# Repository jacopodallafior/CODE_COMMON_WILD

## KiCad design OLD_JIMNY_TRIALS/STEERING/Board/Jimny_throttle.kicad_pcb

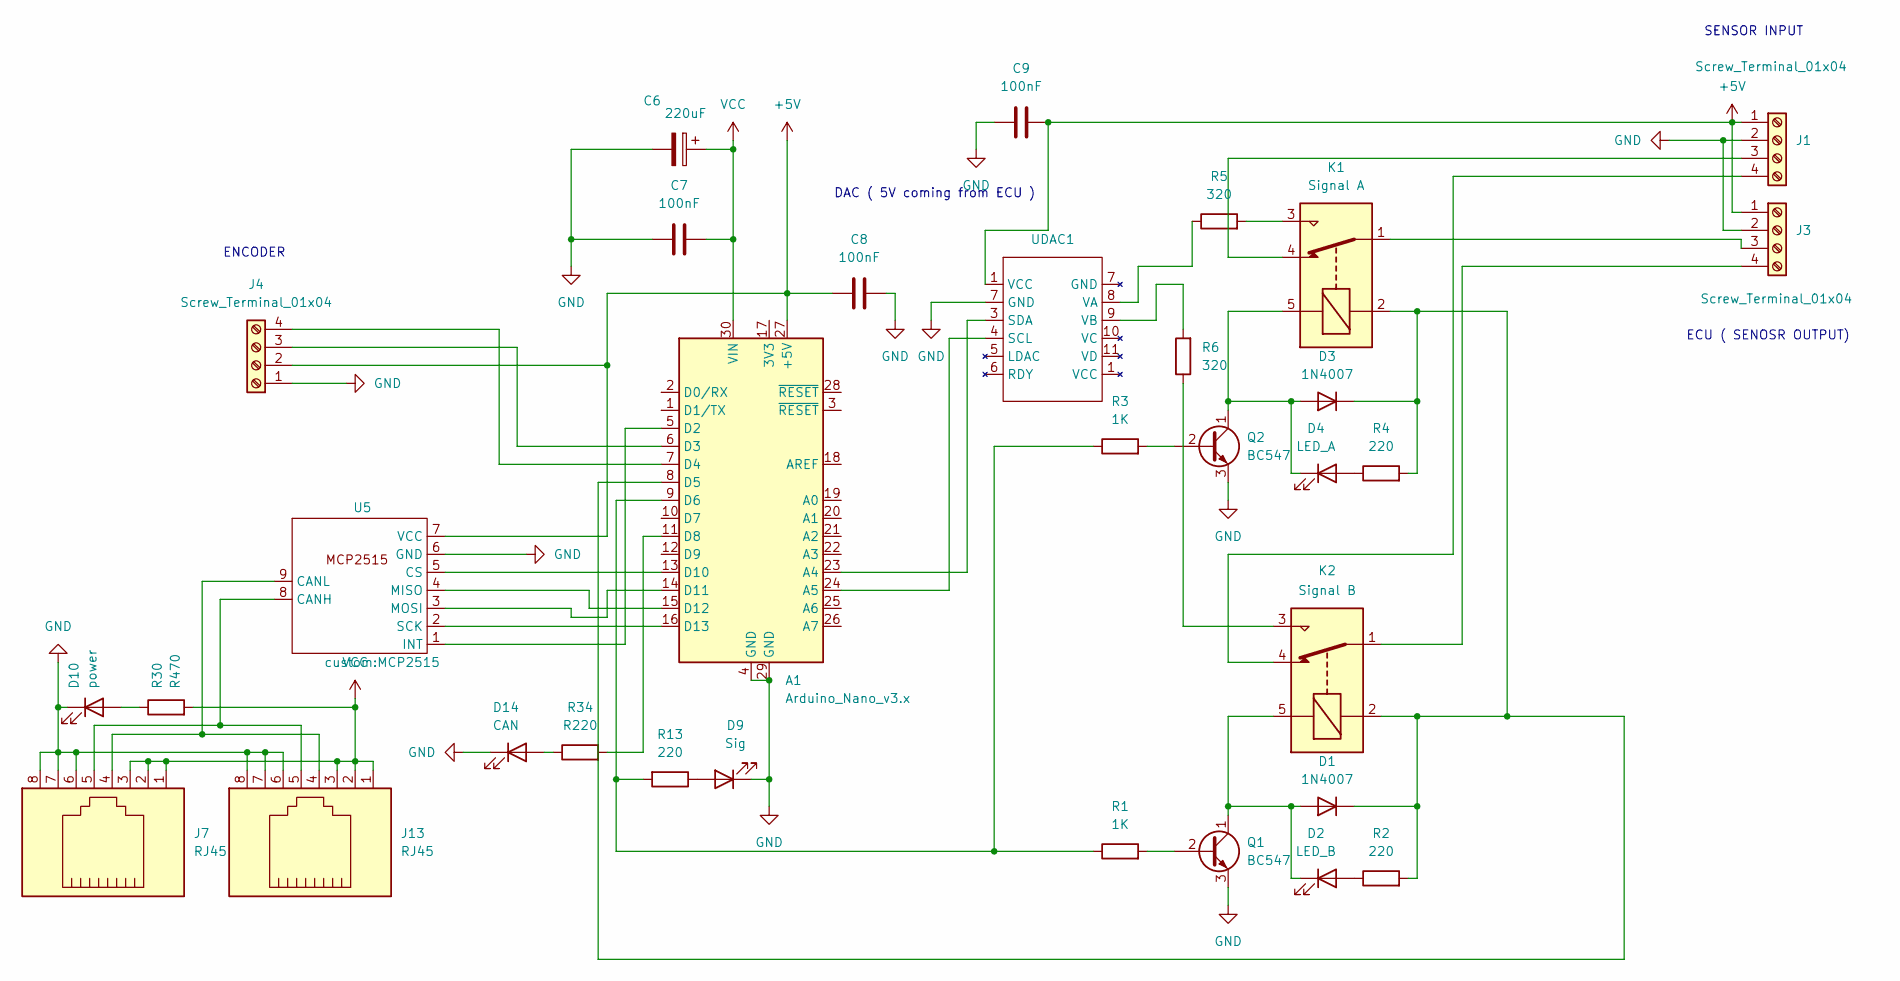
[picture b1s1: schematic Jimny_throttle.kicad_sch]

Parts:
A1: Arduino_Nano_v3.x; Arduino_Nano
C6: 220uF; CP_Radial_D8.0mm_P3.50mm
C7, C8, C9: 100nF; C_Rect_L4.6mm_W2.0mm_P2.50mm_MKS02_FKP02
D1, D3: 1N4007; D_DO-41_SOD81_P10.16mm_Horizontal
D2: LED_B; LED_D5.0mm
D4: LED_A; LED_D5.0mm
D9: Sig; LED_D5.0mm
D10: power; LED_D5.0mm
D14: CAN; LED_D5.0mm
J1, J3, J4: Screw_Terminal_01x04; TerminalBlock_Phoenix_MKDS-1,5-4_1x04_P5.00mm_Horizontal
J7, J13: RJ45; RJ45_OST_PJ012-8P8CX_Vertical
K1: Signal A; Relay_SPDT_SANYOU_SRD_Series_Form_C
K2: Signal B; Relay_SPDT_SANYOU_SRD_Series_Form_C
Q1, Q2: BC547; TO-92_Inline
R1, R3: 1K; R_Axial_DIN0207_L6.3mm_D2.5mm_P10.16mm_Horizontal
R2, R4, R13: 220; R_Axial_DIN0207_L6.3mm_D2.5mm_P10.16mm_Horizontal
R5, R6: 320; R_Axial_DIN0207_L6.3mm_D2.5mm_P10.16mm_Horizontal
R30: R470; R_Axial_DIN0207_L6.3mm_D2.5mm_P7.62mm_Horizontal
R34: R220; R_Axial_DIN0207_L6.3mm_D2.5mm_P7.62mm_Horizontal
U5: MCP2515
UDAC1: DACPIN

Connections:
+5V: A1.27 (+5V), C8.1, C9.2, J1.1, J3.1, J4.2, U5.7 (VCC), UDAC1.1 (VCC)
GND: A1.4 (GND), A1.29 (GND), C6.2, C7.1, C8.2, C9.1, D9.1 (K), D10.1 (K), D14.1 (K), J1.2, J3.2, J4.1, J7.6, J7.7, J7.8, J13.6, J13.7, J13.8, Q1.3 (E), Q2.3 (E), U5.6 (GND), UDAC1.7 (GND); also elsewhere on the board
unnamed: A1.23 (A4), UDAC1.3 (SDA)
unnamed: A1.24 (A5), UDAC1.4 (SCL)
unnamed: A1.5 (D2), U5.1 (INT)
unnamed: A1.6 (D3), J4.3
unnamed: A1.7 (D4), J4.4
unnamed 7: A1.8 (D5), D1.1 (K), D3.1 (K), K1.2, K2.2, R2.2, R4.2; also elsewhere on the board
unnamed: A1.9 (D6), R1.1, R3.1, R13.2
unnamed: A1.11 (D8), R34.2
unnamed: A1.13 (D10), U5.5 (CS)
unnamed: A1.14 (D11), U5.3 (MOSI)
unnamed: A1.15 (D12), U5.4 (MISO)
unnamed: A1.16 (D13), U5.2 (SCK)
unnamed: D1.2 (A), D2.1 (K), K2.5, Q1.1 (C)
unnamed: D2.2 (A), R2.1
unnamed: D3.2 (A), D4.1 (K), K1.5, Q2.1 (C)
unnamed: D4.2 (A), R4.1
unnamed: D9.2 (A), R13.1
unnamed: D10.2 (A), R30.1
unnamed: D14.2 (A), R34.1
unnamed: J1.3, K1.4
unnamed: J1.4, K2.4
unnamed: J3.3, K1.1
unnamed: J3.4, K2.1
unnamed: K1.3, R5.2
unnamed: K2.3, R6.1
unnamed: Q1.2 (B), R1.2
unnamed: Q2.2 (B), R3.2
unnamed: J7.5, J13.5, U5.8 (CANH)
unnamed: J7.4, J13.4, U5.9 (CANL)
unnamed: R5.1, UDAC1.8 (VA)
unnamed: R6.2, UDAC1.9 (VB)
VCC: A1.30 (VIN), C6.1, C7.2, J7.1, J7.2, J7.3, J13.1, J13.2, J13.3, R30.2

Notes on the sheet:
SENSOR INPUT
ECU ( SENOSR OUTPUT)
ENCODER
DAC ( 5V coming from ECU )

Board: 2 copper layers, 33 parts (0 on the bottom side), 34 nets, no tracks yet.

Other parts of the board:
R10: 4.7K; R_Axial_DIN0207_L6.3mm_D2.5mm_P10.16mm_Horizontal

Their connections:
GND: R10.2; also elsewhere on the board
unnamed 7: R10.1; also elsewhere on the board

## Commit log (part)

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2026-03-20 Add readme for JIMNY steering system
2026-03-20 Update schematic images and file extension
    Removed old schematic images and updated the file extension for the system schematic.
2026-03-21 Create A
2026-03-26 Rename Screenshot 2026-03-26 114009.png to Screenshot.png
2026-04-01 Re-add SPI and MCP2515 includes and reset variables
2026-04-03 Add axelBrake_without_ardupid.ino for braking control
2026-04-06 Add throttle testing script for Jimny
    This script allows manual control of the Jimny throttle via the Serial Monitor, enabling users to set throttle percentage values.
2026-04-06 Rename test_throtle to test_throtle.ino
2026-04-20 Refactor brake control logic and add emergency handling
2026-04-20 Enhance board health monitoring and feedback handling
    Added functionality to monitor board health and feedback from critical components.
2026-04-20 Refactor sterfBoard.ino for improved structure
2026-04-20 Implement command timeout handling for EMERGENCY mode
    Added command timeout handling to switch to EMERGENCY mode if no acknowledgment is received.
2026-04-20 Implement brake CAN anti-spam logic
    Added anti-spam logic for brake CAN messages to reduce frequency and ensure significant changes are sent.
2026-04-21 Change encoder pins to D4 and D5
    Updated encoder pins from A3 and A1 to D4 and D5.
2026-04-27 Create original architecture overview document
    Add detailed architecture overview for Jimny autonomous vehicle system.
2026-04-27 Rename original_architecture_overview to original_architecture_overview.md
2026-04-27 readme for general instructions of the previous interns total architecture
2026-04-29 Add hardware update completion report
    Added a detailed hardware update report including changes to files, directory structure, and critical hardware updates. Documented next steps for implementation and verification.
2026-05-04 Create FINAL
2026-05-26 Document SSH connection steps for Jetson
    Added instructions for connecting to Jetson via SSH and running rc jimny.
2026-05-26 Revise SSH and device connection instructions
    Updated instructions for connecting USB devices and running ROS2 nodes on Jetson.
2026-05-26 Update HOWTO_SSH_JETSON
2026-05-27 Revise SSH setup instructions for Jetson
    Updated instructions for connecting USB cables to Jetson.
